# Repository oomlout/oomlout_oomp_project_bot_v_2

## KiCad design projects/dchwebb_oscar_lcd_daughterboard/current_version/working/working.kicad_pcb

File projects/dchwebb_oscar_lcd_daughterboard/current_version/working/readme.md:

# oscar
 
## summary 
* id: dchwebb_oscar_lcd_daughterboard
* user: dchwebb
* name: oscar
* board: lcd_daughterboard
* repo: https://github.com/dchwebb/Oscar
* src_file_repo_kicad_pcb: Hardware/lcd_Daughterboard.kicad_pcb
* src_file_repo_kicad_pcb_link: https://github.com/dchwebb/Oscar/tree/master/Hardware/lcd_Daughterboard.kicad_pcb
* src_file_repo_kicad_sch: Hardware/oscar.kicad_sch
* src_file_repo_kicad_sch_link: https://github.com/dchwebb/Oscar/tree/master/Hardware/oscar.kicad_sch

* src_file_repo_sch: Hardware/lcd_Daughterboard.sch
* src_file_repo_sch_link: https://github.com/dchwebb/Oscar/tree/master/Hardware/lcd_Daughterboard.sch
* full details link: https://github.com/oomlout/oomlout_oomp_project_bot_v_2/tree/main/projects/dchwebb_oscar_lcd_daughterboard/current_version/working

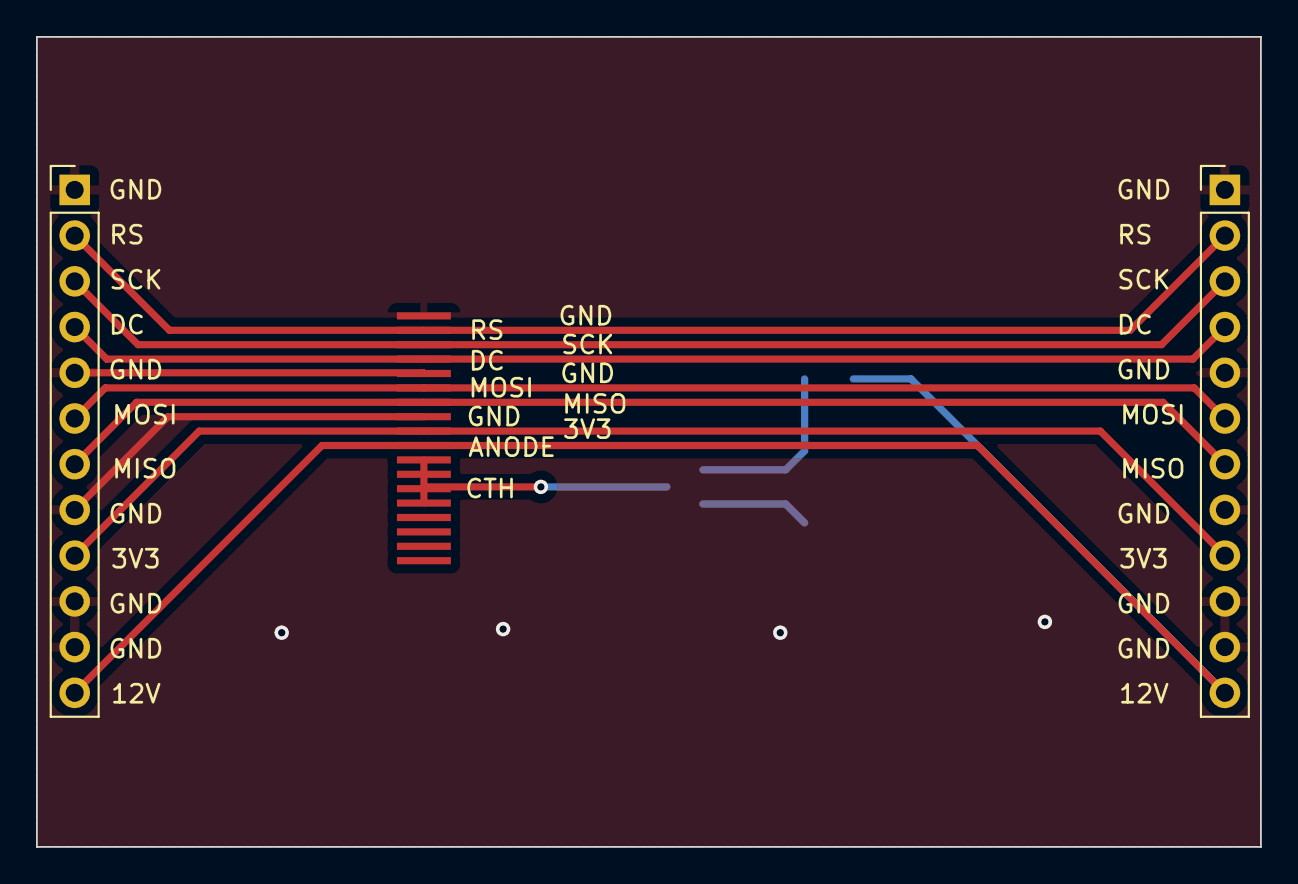
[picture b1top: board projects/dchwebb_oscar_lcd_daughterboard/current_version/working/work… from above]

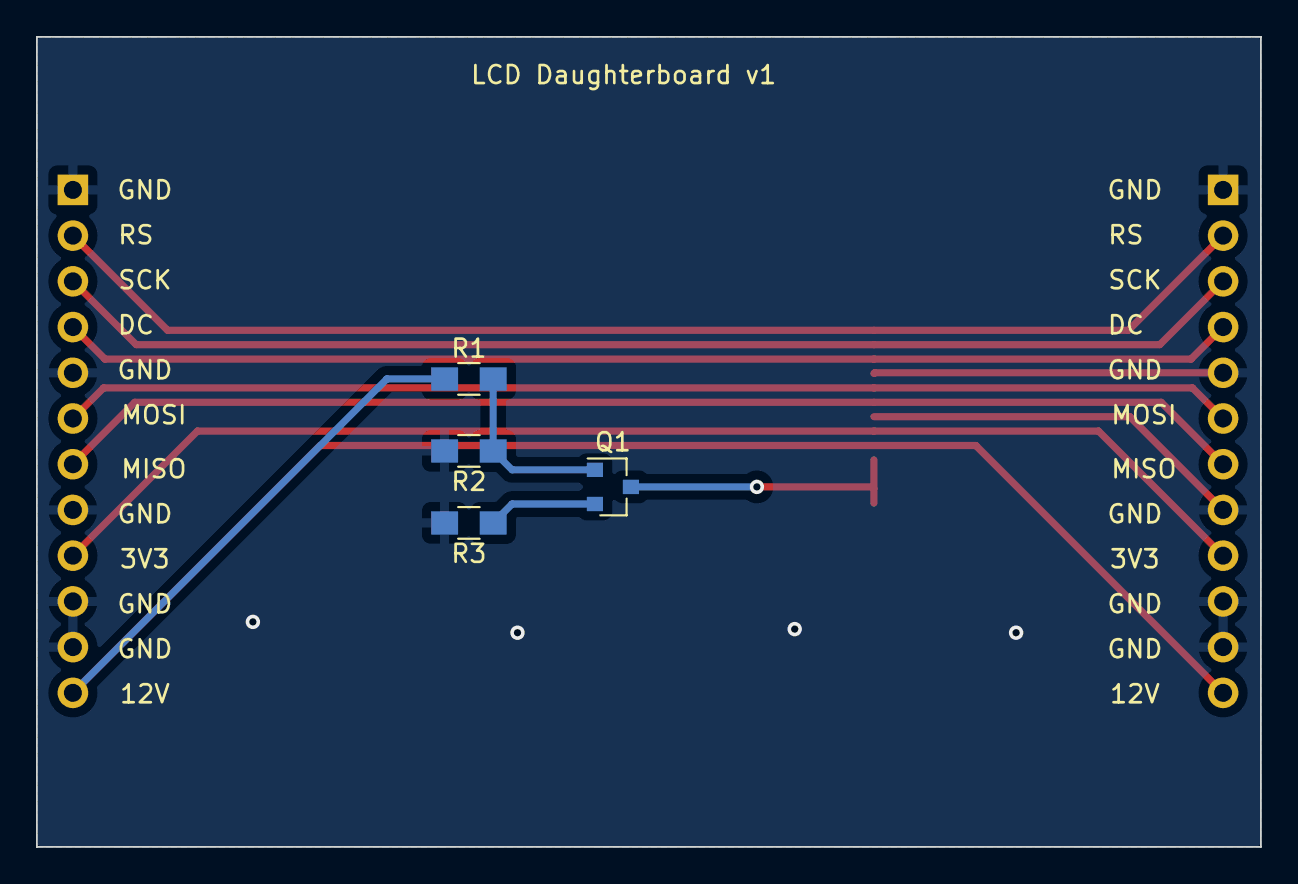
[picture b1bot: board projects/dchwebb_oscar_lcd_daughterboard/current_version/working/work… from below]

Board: 2 copper layers, 68.0 x 45.0 mm, 7 parts (4 on the bottom side), 11 nets.

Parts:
J1, J2: Conn_01x12; Pin_Header_Straight_1x12_Pitch2.54mm
Q1: MMBT3904; SOT-23
R1: 220; R_0805_HandSoldering
R2: 1k; R_0805_HandSoldering
R3: 100; R_0805_HandSoldering
U1: ILI9341_SPI_Bare; 18x0.8mmLCDConnector

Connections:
+3V3: J1.9, J2.9, U1.9
GND: J1.1, J1.5, J1.8, J1.10, J1.11, J2.1, J2.5, J2.8, J2.10, J2.11, R2.2, R3.2, U1.1, U1.5, U1.8
LCD_CATHODE: Q1.3, U1.11, U1.12, U1.13, U1.14
LCD_DC: J1.4, J2.4, U1.4
LCD_MISO: J1.7, J2.7, U1.7
LCD_MOSI: J1.6, J2.6, U1.6
LCD_RESET: J1.2, J2.2, U1.2
LCD_SCK: J1.3, J2.3, U1.3
unnamed: Q1.1, R1.2, R2.1
unnamed: Q1.2, R3.1
VCC: J1.12, J2.12, R1.1, U1.10

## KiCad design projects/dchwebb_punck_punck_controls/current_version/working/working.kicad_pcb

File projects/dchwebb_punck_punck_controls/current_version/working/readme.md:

# punck
 
## summary 
* id: dchwebb_punck_punck_controls
* user: dchwebb
* name: punck
* board: punck_controls
* repo: https://github.com/dchwebb/Punck
* src_file_repo_kicad_pcb: Hardware_v1_1/Punck_Components.kicad_pcb
* src_file_repo_kicad_pcb_link: https://github.com/dchwebb/Punck/tree/main/Hardware_v1_1/Punck_Components.kicad_pcb
* src_file_repo_kicad_sch: Hardware_v1_1/Punck_Components.kicad_sch
* src_file_repo_kicad_sch_link: https://github.com/dchwebb/Punck/tree/main/Hardware_v1_1/Punck_Components.kicad_sch

* src_file_repo_sch: 
* src_file_repo_sch_link: https://github.com/dchwebb/Punck/tree/main/
* full details link: https://github.com/oomlout/oomlout_oomp_project_bot_v_2/tree/main/projects/dchwebb_punck_punck_controls/current_version/working

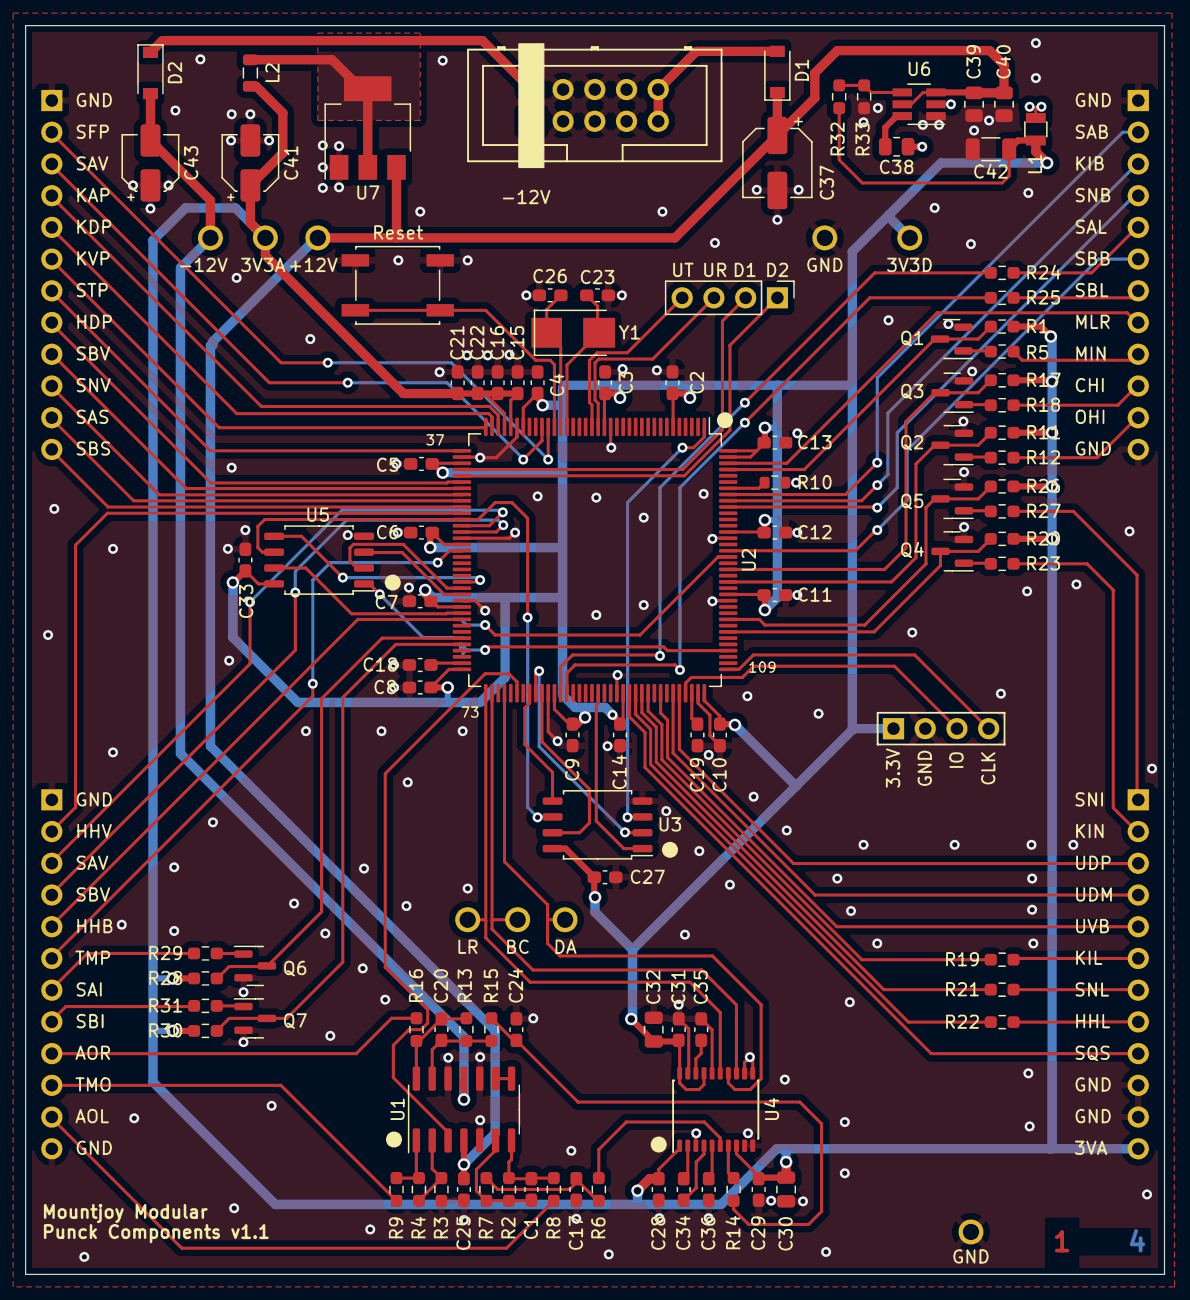
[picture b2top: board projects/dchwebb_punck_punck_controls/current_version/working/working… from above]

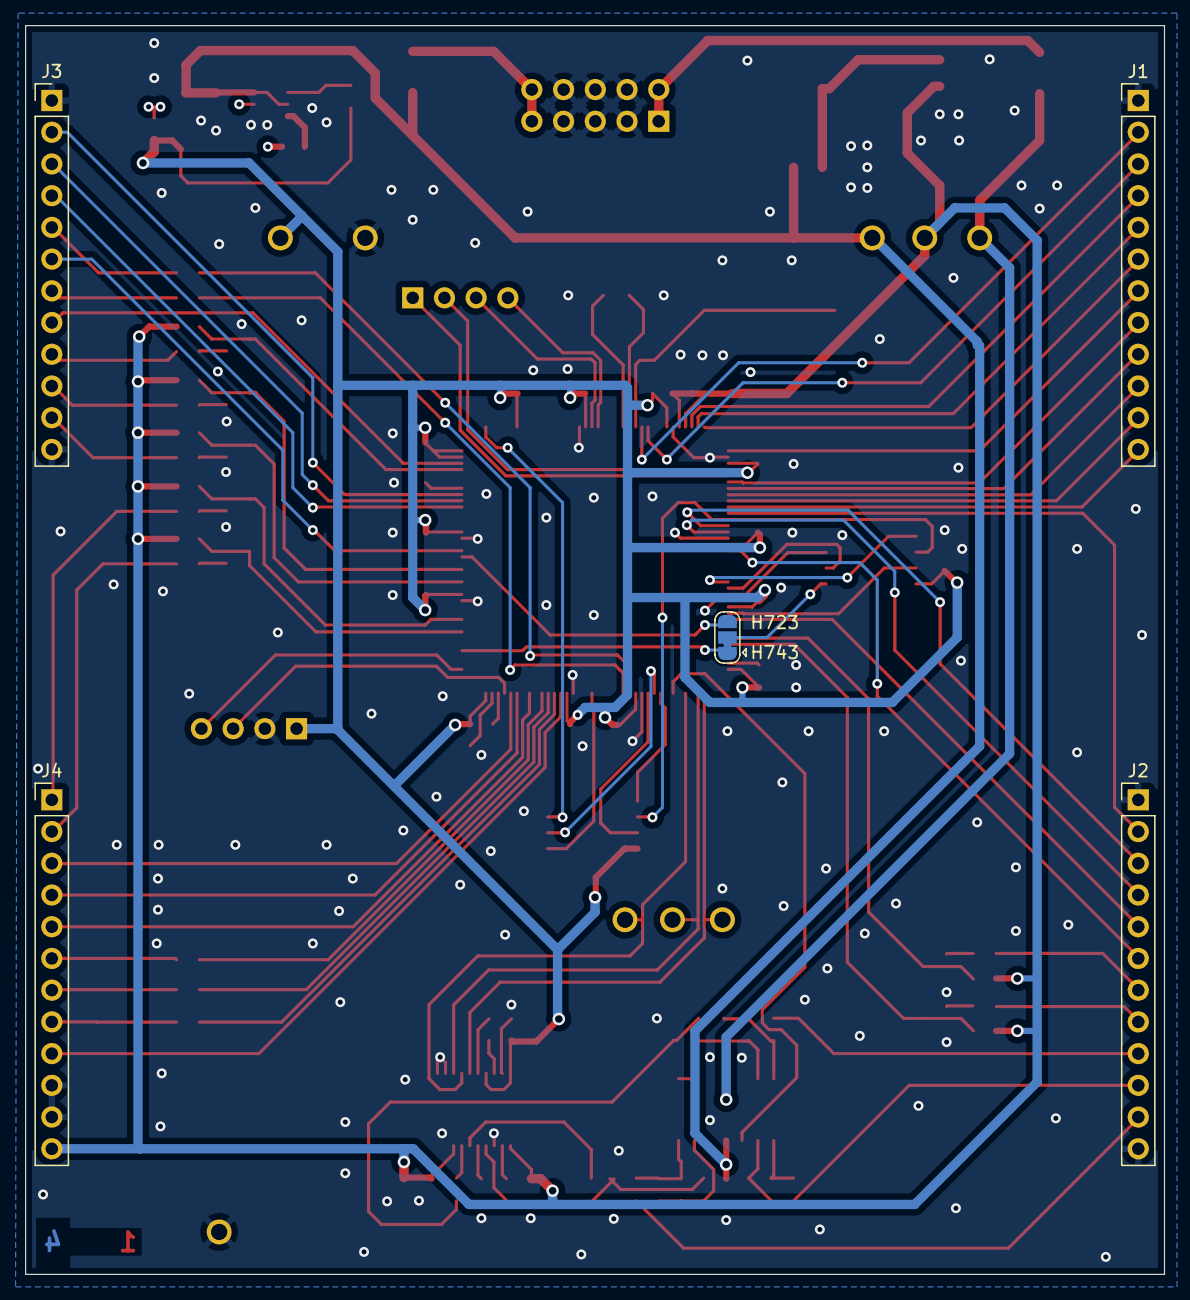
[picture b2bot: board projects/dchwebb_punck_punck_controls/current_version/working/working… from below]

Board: 4 copper layers, 91.2 x 100.0 mm, 114 parts (5 on the bottom side), 114 nets.

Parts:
C1, C20: 100pF; C_0603_1608Metric_Pad1.08x0.95mm_HandSolder
C2: 4.7uF; C_0603_1608Metric_Pad1.08x0.95mm_HandSolder
C3, C4, C5, C6, C7, C8, C9, C10, C11, C12, C13, C14, C15, C22, C27, C28, C29, C31, C33, C35: 100nF; C_0603_1608Metric_Pad1.08x0.95mm_HandSolder
C16, C21: 1uF; C_0603_1608Metric_Pad1.08x0.95mm_HandSolder
C17, C24: 2n2; C_0603_1608Metric_Pad1.08x0.95mm_HandSolder
C18, C19, C25, C34, C36: 2.2uF; C_0603_1608Metric_Pad1.08x0.95mm_HandSolder
C23, C26: 30pF; C_0603_1608Metric_Pad1.08x0.95mm_HandSolder
C30, C32: 10uF; C_0805_2012Metric
C37: 47uF; CP_Elec_5x5.8
C38: 100nF; R_0805_2012Metric
C39, C40: 10uF; R_0805_2012Metric
C41, C43: 22uF; CP_Elec_4x5.8
C42: 47uF; R_1206_3216Metric
D1, D2: 1N5819; D_SOD-123
FID1: 4_Layer_Marker; 4_Layer_Markers
J1, J2, J3, J4: Conn_01x12_Female; PinHeader_1x12_P2.54mm_Vertical
J5: Debug_Header; PinHeader_1x04_P2.54mm_Vertical
J6: SWD_Header; SWD_header
J7: Eurorack_10_pin_power; Eurorack_10_pin_header
JP1: QSPI2_NCS_Select; SolderJumper-3_P1.3mm_Bridged12_RoundedPad1.0x1.5mm
L1: 3.3uH; L_0806
L2: L; L_0805_2012Metric
Q1, Q2, Q3, Q4, Q5, Q6, Q7: MMBT3904; SOT-23
R1, R5, R11, R12, R17, R18, R20, R23, R26, R27, R28, R29, R30, R31: 4k7; R_0603_1608Metric_Pad0.98x0.95mm_HandSolder
R2, R13: 47k; R_0603_1608Metric_Pad0.98x0.95mm_HandSolder
R3, R7, R15: 15k; R_0603_1608Metric_Pad0.98x0.95mm_HandSolder
R4, R33: 10k; R_0603_1608Metric_Pad0.98x0.95mm_HandSolder
R6, R8, R9, R14, R16: 1k; R_0603_1608Metric_Pad0.98x0.95mm_HandSolder
R10: 100k; R_0603_1608Metric
R19, R21, R22, R24, R25: 560; R_0603_1608Metric_Pad0.98x0.95mm_HandSolder
R32: 33k; R_0603_1608Metric_Pad0.98x0.95mm_HandSolder
RESET1: SW_Push; SW_SPST_EVQQ2
TP1, TP2, TP3, TP4, TP5, TP6, TP7, TP8, TP9: TestPoint; 1.3mm_Test_Point
U1: TL074; SOIC-14_3.9x8.7mm_P1.27mm
U2: STM32H743ZITx; LQFP-144_20x20mm_P0.5mm
U3, U5: W25Q128JVS; SOIC-8_5.23x5.23mm_P1.27mm
U4: PCM5100APW; SSOP-20_4.4x6.5mm_Pitch0.65mm_Round_Pads
U6: TPS561201; SOT-23-6_Handsoldering
U7: LD1117-3.3-4Tab; SOT-223-3_TabPin2
Y1: 8MHz 20pF; Crystal_SMD_5032-2Pin_5.0x3.2mm

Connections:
+3.3VA: C15.2, C16.2, C21.2, C22.2, C28.1, C29.1, C30.1, C41.1, J4.12, L2.1, R1.2, R11.2, R17.2, R20.2, R26.2, R28.2, R30.2, TP6.1, U2.32 (VREF+), U2.33 (VDDA), U4.1 (CPVDD), U4.8 (AVDD)
+3V3: C2.2, C3.2, C4.2, C5.2, C6.2, C7.2, C8.2, C9.2, C10.2, C11.2, C12.2, C13.2, C14.2, C27.1, C31.1, C32.1, C33.1, C42.1, J6.1, L1.2, R32.1, TP5.1, U2.6 (VBAT), U2.17 (VDD), U2.30 (VDD), U2.39 (VDD), U2.52 (VDD), U2.62 (VDD), U2.72 (VDD), U2.84 (VDD), U2.95 (VDD33_USB), U2.108 (VDD), U2.121 (VDD), U2.131 (VDD), U2.143 (PDR_ON), U2.144 (VDD), U3.8 (VCC), U4.17 (XSMT), U4.20 (DVDD), U5.8 (VCC)
+12V: D1.2 (A), J7.9, J7.10
-12V: D2.1 (K), J7.1, J7.2
/AUDIO_OUT_L: J2.11, R8.2
/AUDIO_OUT_R: J2.9, R16.2
/CB: C38.2, U6.6 (VBST)
/CH_CLAMP: Q3.3 (C), R17.1, U2.125 (PG10)
/CH_IN: J3.10, R18.1
/DAC1: J5.2, U2.40 (PA4)
/DAC2: J5.1, U2.41 (PA5)
/DAC_BCLK: TP3.1, U2.74 (PB13), U4.13 (BCK)
/DAC_DATA: TP2.1, U2.76 (PB15), U4.14 (DIN)
/DAC_LRCLK: TP1.1, U2.73 (PB12), U4.15 (LRCK)
/DAC_OUT_L: R6.2, U4.6 (OUTL)
/DAC_OUT_R: R14.2, U4.7 (OUTR)
/FB: R32.2, R33.1, U6.4 (VFB)
/HH_BTN: J2.5, U2.64 (PE11)
/HH_LED: J4.8, R22.1
/HH_LED_OUT: R22.2, U2.97 (PC7)
/HIHAT_DECAY_POT: J1.8, U2.42 (PA6)
/HIHAT_VOL_POT: J2.2, U2.47 (PB1)
/KICK_ATTACK_POT: J1.4, U2.34 (PA0)
/KICK_CLAMP: Q4.3 (C), R20.1, U2.115 (PD1)
/KICK_DECAY_POT: J1.5, U2.35 (PA1)
/KICK_IN: J4.2, R23.1
/KICK_VOL_POT: J1.6, U2.36 (PA2)
/KI_BTN: J3.3, U2.136 (PB6)
/KI_LED: J4.6, R19.1
/KI_LED_OUT: R19.2, U2.99 (PC9)
/MIDI_IN: J3.9, R5.1
/MIDI_LEARN: J3.8, U2.142 (PE1)
/MIDI_UART: Q1.3 (C), R1.1, U2.141 (PE0)
/OCTOSPIM_P2_NCS: JP1.3 (B), U2.127 (PG12)
/OH_CLAMP: Q2.3 (C), R11.1, U2.123 (PD7)
/OH_IN: J3.11, R12.1
/QSPI_BK1_IO0: U2.80 (PD11), U3.5 (DI(IO0))
/QSPI_BK1_IO1: U2.81 (PD12), U3.2 (DO(IO1))
/QSPI_BK1_IO2: U2.1 (PE2), U3.3 (IO2)
/QSPI_BK1_IO3: U2.82 (PD13), U3.7 (IO3)
/QSPI_BK1_NCS: U2.91 (PG6), U3.1 (~CS)
/QSPI_BK2_IO0: U2.58 (PE7), U5.5 (DI(IO0))
/QSPI_BK2_IO1: U2.59 (PE8), U5.2 (DO(IO1))
/QSPI_BK2_IO2: U2.60 (PE9), U5.3 (IO2)
/QSPI_BK2_IO3: U2.63 (PE10), U5.7 (IO3)
/QSPI_BK2_NCS: JP1.1 (A), U2.112 (PC11)
/QSPI_CLK: U2.48 (PB2), U3.6 (CLK), U5.6 (CLK)
/SAMPLER_A_CLAMP: Q6.3 (C), R28.1, U2.67 (PE14)
/SAMPLER_A_IN: J2.7, R29.1
/SAMPLER_A_SPEED_POT: J1.11, U2.45 (PC5)
/SAMPLER_A_VOICE_POT: J1.3, U2.27 (PC1)
/SAMPLER_A_VOL_POT: J2.3, U2.49 (PF11)
/SAMPLER_B_CLAMP: Q7.3 (C), R30.1, U2.68 (PE15)
/SAMPLER_B_IN: J2.8, R31.1
/SAMPLER_B_SPEED_POT: J1.12, U2.46 (PB0)
/SAMPLER_B_VOICE_POT: J1.9, U2.43 (PA7)
/SAMPLER_B_VOL_POT: J2.4, U2.50 (PF12)
/SA_BTN: J3.2, U2.137 (PB7)
/SA_LED: J3.5, R24.1
/SA_LED_OUT: R24.2, U2.85 (PD14)
/SB_BTN: J3.6, U2.128 (PG13)
/SB_LED: J3.7, R25.1
/SB_LED_OUT: R25.2, U2.86 (PD15)
/SEQ_SELECT: J4.9, U2.96 (PC6)
/SNARE_CLAMP: Q5.3 (C), R26.1, U2.117 (PD3)
/SNARE_FILTER_POT: J1.2, U2.26 (PC0)
/SNARE_IN: J4.1, R27.1
/SNARE_TUNING_POT: J1.7, U2.37 (PA3)
/SNARE_VOL_POT: J1.10, U2.44 (PC4)
/SN_BTN: J3.4, U2.135 (PB5)
/SN_LED: J4.7, R21.1
/SN_LED_OUT: R21.2, U2.98 (PC8)
/SWCLK: J6.4, U2.109 (PA14)
/SWIO: J6.3, U2.105 (PA13)
/TEMPO_CLOCK: U1.3 (+), U2.78 (PD9)
/TEMPO_OUT: J2.10, R9.2
/TEMPO_POT: J2.6, U2.53 (PF13)
/UART_RX: J5.3, U2.18 (PF6)
/UART_TX: J5.4, U2.19 (PF7)
/USB_DM: J4.4, U2.103 (PA11)
/USB_DP: J4.3, U2.104 (PA12)
/USB_VBUS: J4.5, U2.101 (PA9)
/VO: L2.2, U7.2 (VO)
/VSW: C38.1, L1.1, U6.2 (SW)
GND: C2.1, C3.1, C4.1, C5.1, C6.1, C7.1, C8.1, C9.1, C10.1, C11.1, C12.1, C13.1, C14.1, C15.1, C16.1, C17.2, C18.2, C19.2, C21.1, C22.1, C23.2, C24.2, C25.2, C26.2, C27.2, C28.2, C29.2, C30.2, C31.2, C32.2, C33.2, C35.1, C36.2, C37.2, C39.2, C40.2, C41.2, C42.2, C43.1, J1.1, J2.1, J2.12, J3.1, J3.12, J4.10, J4.11, J6.2, J7.3, J7.4, J7.5, J7.6, J7.7, J7.8, Q1.2 (E), Q2.2 (E), Q3.2 (E), Q4.2 (E), Q5.2 (E), Q6.2 (E), Q7.2 (E), R3.2, R10.1, R33.2, RESET1.2, TP4.1, TP9.1, U1.5 (+), U1.10 (+), U1.12 (+), U2.16 (VSS), U2.31 (VSSA), U2.38 (VSS), U2.51 (VSS), U2.61 (VSS), U2.83 (VSS), U2.94 (VSS), U2.107 (VSS), U2.120 (VSS), U2.130 (VSS), U3.4 (GND), U4.3 (CPGND), U4.9 (AGND), U4.10 (DEMP), U4.11 (FLT), U4.12 (SCK), U4.16 (FMT), U4.19 (DGND), U5.4 (GND), U6.1 (GND), U7.1 (GND)
unnamed: C1.1, R2.1, R8.1, U1.7
unnamed: C1.2, R2.2, R7.1, U1.6 (-)
unnamed: C17.1, R6.1, R7.2
unnamed: C18.1, U2.71 (VCAP1)
unnamed: C19.1, U2.106 (VCAP2)
unnamed: C20.1, R13.1, R16.1, U1.14
unnamed: C20.2, R13.2, R15.1, U1.13 (-)
unnamed: C23.1, U2.23 (PH0), Y1.2
unnamed: C24.1, R14.1, R15.2
unnamed: C26.1, U2.24 (PH1), Y1.1
unnamed: C34.1, U4.2 (CAPP)
unnamed: C34.2, U4.4 (CAPM)
unnamed: C35.2, U4.18 (LDOO)
unnamed: C36.1, U4.5 (VNEG)
unnamed: JP1.2 (C), U5.1 (~CS)
unnamed: Q1.1 (B), R5.2
unnamed: Q2.1 (B), R12.2
unnamed: Q3.1 (B), R18.2
unnamed: Q4.1 (B), R23.2
unnamed: Q5.1 (B), R27.2
unnamed: Q6.1 (B), R29.2
unnamed: Q7.1 (B), R31.2
unnamed: R3.1, R4.2, U1.2 (-)
unnamed: R4.1, R9.1, U1.1
unnamed: R10.2, U2.138 (BOOT0)
unnamed: RESET1.1, U2.25 (NRST)
unnamed: U1.8, U1.9 (-)
VCC: C25.1, C37.1, C39.1, C40.1, D1.1 (K), TP7.1, U1.4 (V+), U6.3 (VIN), U6.5 (EN), U7.3 (VI)
VEE: C43.2, D2.2 (A), TP8.1, U1.11 (V-)

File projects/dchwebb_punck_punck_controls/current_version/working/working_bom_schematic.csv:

"Source:","C:\gh\oomlout_oomp_project_bot_v_2\projects\dchwebb_punck_punck_controls\current_version\working\working.kicad_sch"
"Date:","01/10/2023 02:41:31"
"Tool:","Eeschema 7.0.6"
"Generator:","C:/Program Files/KiCad/7.0/bin/scripting/plugins/bom_csv_grouped_by_value_with_fp.py"
"Component Count:","114"
"Ref","Qnty","Value","Cmp name","Footprint","Description","Vendor","DNP"
"C1, C20","2","100pF","C_Small","Capacitor_SMD:C_0603_1608Metric_Pad1.08x0.95mm_HandSolder","Unpolarized capacitor, small symbol","",""
"C2","1","4.7uF","C_Small","Capacitor_SMD:C_0603_1608Metric_Pad1.08x0.95mm_HandSolder","Unpolarized capacitor, small symbol","",""
"C3, C4, C5, C6, C7, C8, C9, C10, C11, C12, C13, C14, C15, C22, C27, C28, C29, C31, C33, C35","20","100nF","C_Small","Capacitor_SMD:C_0603_1608Metric_Pad1.08x0.95mm_HandSolder","Unpolarized capacitor, small symbol","",""
"C16, C21","2","1uF","C_Small","Capacitor_SMD:C_0603_1608Metric_Pad1.08x0.95mm_HandSolder","Unpolarized capacitor, small symbol","",""
"C17, C24","2","2n2","C_Small","Capacitor_SMD:C_0603_1608Metric_Pad1.08x0.95mm_HandSolder","Unpolarized capacitor, small symbol","",""
"C18, C19, C25, C34, C36","5","2.2uF","C_Small","Capacitor_SMD:C_0603_1608Metric_Pad1.08x0.95mm_HandSolder","Unpolarized capacitor, small symbol","",""
"C23, C26","2","30pF","C_Small","Capacitor_SMD:C_0603_1608Metric_Pad1.08x0.95mm_HandSolder","Unpolarized capacitor, small symbol","",""
"C30, C32, C39, C40","4","10uF","C_Small","Capacitor_SMD:C_0805_2012Metric","Unpolarized capacitor, small symbol","",""
"C37","1","47uF","C_Polarized_Small","Capacitor_SMD:CP_Elec_5x5.8","Polarized capacitor, small symbol","",""
"C38","1","100nF","C_Small","Capacitor_SMD:C_0805_2012Metric","Unpolarized capacitor, small symbol","",""
"C41, C43","2","22uF","C_Polarized_Small","Capacitor_SMD:CP_Elec_4x5.8","Polarized capacitor, small symbol","",""
"C42","1","47uF","C_Small","Resistor_SMD:R_1206_3216Metric","Unpolarized capacitor, small symbol","",""
"D1, D2","2","1N5819","1N5819","Diode_SMD:D_SOD-123","40V 1A Schottky Barrier Rectifier Diode, DO-41","",""
"FID1","1","4_Layer_Marker","Fiducial","Custom_Footprints:4_Layer_Markers","Fiducial Marker","",""
"J1, J2, J3, J4","4","Conn_01x12_Female","Conn_01x12_Female","Connector_PinHeader_2.54mm:PinHeader_1x12_P2.54mm_Vertical","Generic connector, single row, 01x12, script generated (kicad-library-utils/schlib/autogen/connector/)","",""
"J5","1","Debug_Header","Conn_01x04_Female","Connector_PinHeader_2.54mm:PinHeader_1x04_P2.54mm_Vertical","Generic connector, single row, 01x04, script generated (kicad-library-utils/schlib/autogen/connector/)","",""
"J6","1","SWD_Header","Conn_01x04_Male","Custom_Footprints:SWD_header","Generic connector, single row, 01x04, script generated (kicad-library-utils/schlib/autogen/connector/)","",""
"J7","1","Eurorack_10_pin_power","Eurorack_10_pin_power","Custom_Footprints:Eurorack_10_pin_header","","",""
"JP1","1","QSPI2_NCS_Select","SolderJumper_3_Bridged12","Jumper:SolderJumper-3_P1.3mm_Bridged12_RoundedPad1.0x1.5mm","3-pole Solder Jumper, pins 1+2 closed/bridged","",""
"L1","1","3.3uH","L_Small","Custom_Footprints:L_0806","Inductor, small symbol","",""
"L2","1","L","L","Inductor_SMD:L_0805_2012Metric","Inductor","",""
"Q1, Q2, Q3, Q4, Q5, Q6, Q7","7","MMBT3904","MMBT3904","Package_TO_SOT_SMD:SOT-23","0.2A Ic, 40V Vce, Small Signal NPN Transistor, SOT-23","",""
"R1, R5, R11, R12, R17, R18, R20, R23, R26, R27, R28, R29, R30, R31","14","4k7","R_Small","Resistor_SMD:R_0603_1608Metric_Pad0.98x0.95mm_HandSolder","Resistor, small symbol","",""
"R2, R13","2","47k","R","Resistor_SMD:R_0603_1608Metric_Pad0.98x0.95mm_HandSolder","Resistor","",""
"R3, R7, R15","3","15k","R","Resistor_SMD:R_0603_1608Metric_Pad0.98x0.95mm_HandSolder","Resistor","",""
"R4, R33","2","10k","R_Small","Resistor_SMD:R_0603_1608Metric_Pad0.98x0.95mm_HandSolder","Resistor, small symbol","",""
"R6, R8, R9, R14, R16","5","1k","R_Small","Resistor_SMD:R_0603_1608Metric_Pad0.98x0.95mm_HandSolder","Resistor, small symbol","",""
"R10","1","100k","R_Small","Resistor_SMD:R_0603_1608Metric","Resistor, small symbol","",""
"R19, R21, R22, R24, R25","5","560","R_Small","Resistor_SMD:R_0603_1608Metric_Pad0.98x0.95mm_HandSolder","Resistor, small symbol","",""
"R32","1","33k","R_Small","Resistor_SMD:R_0603_1608Metric_Pad0.98x0.95mm_HandSolder","Resistor, small symbol","",""
"RESET1","1","SW_Push","SW_Push","Custom_Footprints:SW_SPST_EVQQ2","Push button switch, generic, two pins","",""
"TP1, TP2, TP3, TP4, TP5, TP6, TP7, TP8, TP9","9","TestPoint","TestPoint","Custom_Footprints:1.3mm_Test_Point","test point","",""
"U1","1","TL074","TL074","Package_SO:SOIC-14_3.9x8.7mm_P1.27mm","Quad Low-Noise JFET-Input Operational Amplifiers, DIP-14/SOIC-14","",""
"U2","1","STM32H743ZITx","STM32H743ZITx","Package_QFP:LQFP-144_20x20mm_P0.5mm","ARM Cortex-M7 MCU, 2048KB flash, 864KB RAM, 400MHz, 1.7-3.6V, 114 GPIO, LQFP-144","",""
"U3, U5","2","W25Q128JVS","W25Q128JVS","Package_SO:SOIC-8_5.23x5.23mm_P1.27mm","128Mb Serial Flash Memory, Standard/Dual/Quad SPI, SOIC-8","",""
"U4","1","PCM5100APW","PCM5100APW","Custom_Footprints:SSOP-20_4.4x6.5mm_Pitch0.65mm_Round_Pads","2VRMS DirectPath, 100dB Audio Stereo DAC with 32-bit, 384kHz PCM Interface, TSSOP-20","",""
"U6","1","TPS561201","TPS561201","Package_TO_SOT_SMD:SOT-23-6_Handsoldering","1A Synchronous Step-Down Voltage Regulator, Adjustable Output Voltage, 4.5-17V Input Voltage, SOT-23-6","",""
"U7","1","LD1117-3.3-4Tab","LD1117-3.3-4Tab","Package_TO_SOT_SMD:SOT-223-3_TabPin2","1A Low Dropout regulator, positive, 3.3V fixed output, SOT-223","",""
"Y1","1","8MHz 20pF","Crystal","Crystal:Crystal_SMD_5032-2Pin_5.0x3.2mm","Two pin crystal","",""

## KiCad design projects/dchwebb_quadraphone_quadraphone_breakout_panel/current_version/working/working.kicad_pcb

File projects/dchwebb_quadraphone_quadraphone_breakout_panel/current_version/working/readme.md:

# quadraphone
 
## summary 
* id: dchwebb_quadraphone_quadraphone_breakout_panel
* user: dchwebb
* name: quadraphone
* board: quadraphone_breakout_panel
* repo: https://github.com/dchwebb/Quadraphone
* src_file_repo_kicad_pcb: V1_Production/Quadraphone.kicad_pcb
* src_file_repo_kicad_pcb_link: https://github.com/dchwebb/Quadraphone/tree/main/V1_Production/Quadraphone.kicad_pcb
* src_file_repo_kicad_sch: V1_Production/OSCVoice.kicad_sch
* src_file_repo_kicad_sch_link: https://github.com/dchwebb/Quadraphone/tree/main/V1_Production/OSCVoice.kicad_sch

* src_file_repo_sch: 
* src_file_repo_sch_link: https://github.com/dchwebb/Quadraphone/tree/main/
* full details link: https://github.com/oomlout/oomlout_oomp_project_bot_v_2/tree/main/projects/dchwebb_quadraphone_quadraphone_breakout_panel/current_version/working

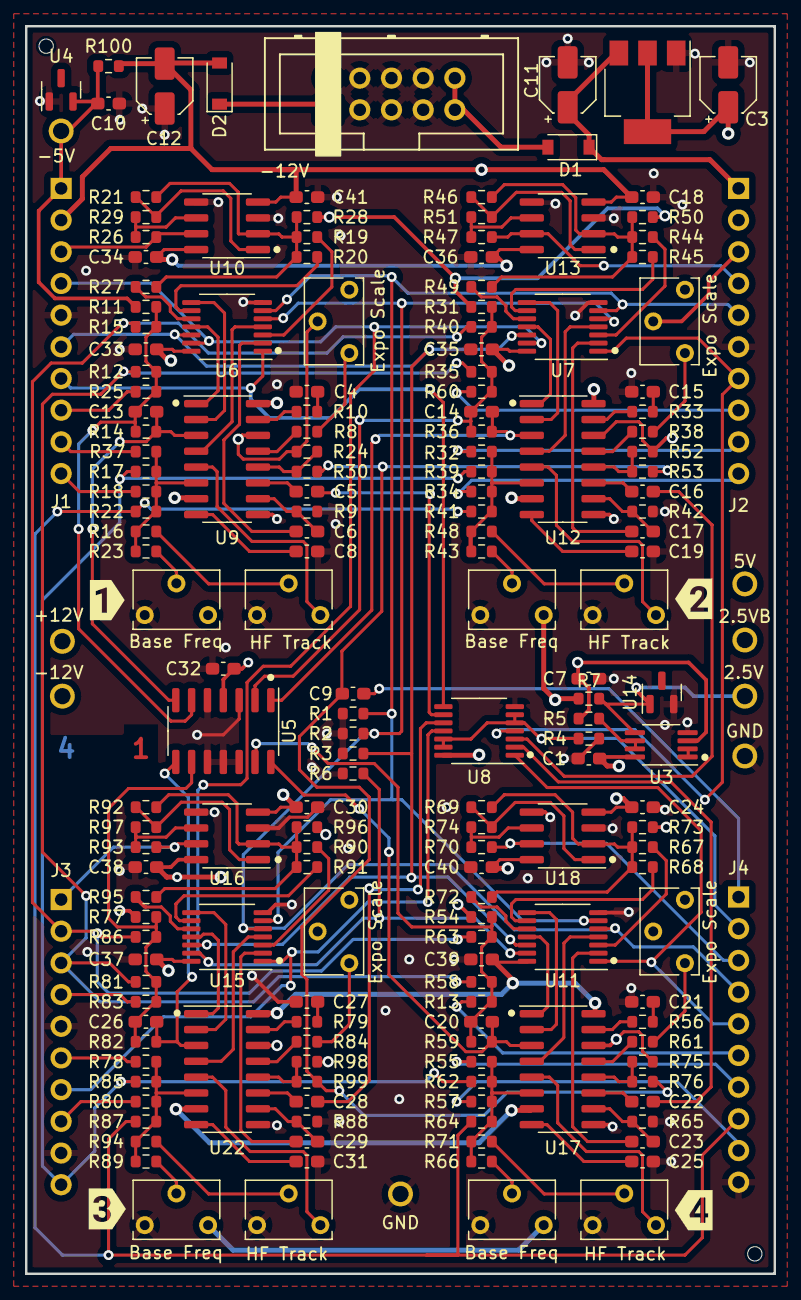
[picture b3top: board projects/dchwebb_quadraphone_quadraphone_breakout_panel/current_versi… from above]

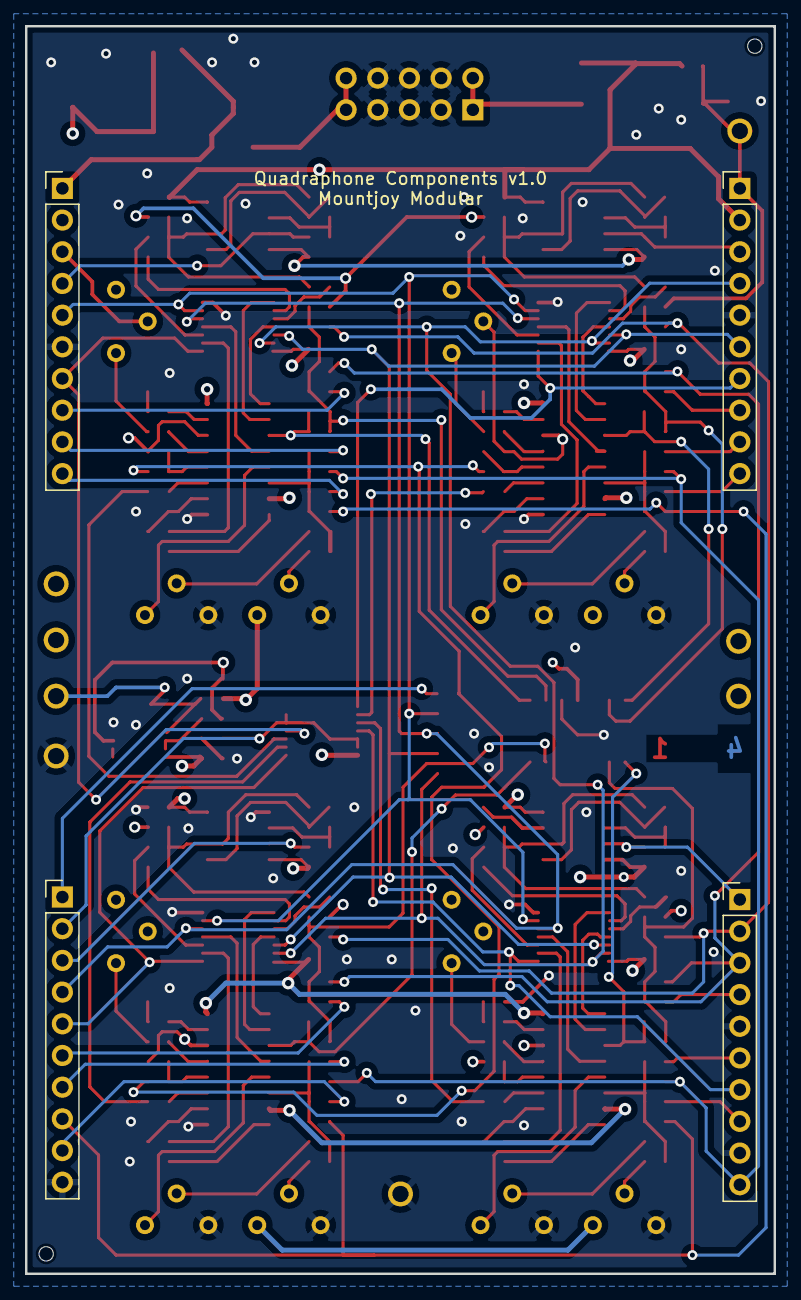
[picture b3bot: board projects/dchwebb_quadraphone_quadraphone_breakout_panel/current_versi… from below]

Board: 4 copper layers, 60.0 x 100.0 mm, 190 parts (4 on the bottom side), 142 nets.

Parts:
Base_Freq_Trim1, Base_Freq_Trim2, Base_Freq_Trim3, Base_Freq_Trim4: 5k; Potentiometer_Bourns_3266W_Vertical
C1, C7, C9: 1uF; C_0603_1608Metric_Pad1.08x0.95mm_HandSolder
C3: 10uF; CP_Elec_4x5.7
C4, C5, C6, C15, C16, C17, C21, C22, C23, C27, C28, C29: 10nF; C_0603_1608Metric_Pad1.08x0.95mm_HandSolder
C8, C19, C25, C31: 3.9nF; C_0603_1608Metric_Pad1.08x0.95mm_HandSolder
C10, C18, C24, C30, C32, C33, C34, C35, C36, C37, C38, C39, C40, C41: 100nF; C_0603_1608Metric_Pad1.08x0.95mm_HandSolder
C11, C12: 22uF; CP_Elec_4x5.8
C13, C14, C20, C26: 1nF; C_0603_1608Metric_Pad1.08x0.95mm_HandSolder
D1, D2: 1N5819; D_SOD-123
Expo_Trim1, Expo_Trim2, Expo_Trim3, Expo_Trim4: 5k; Potentiometer_Bourns_3266W_Vertical
FID1: 4_Layer_Marker; 4_Layer_Markers
HF_Track_Trim1, HF_Track_Trim2, HF_Track_Trim3, HF_Track_Trim4: 5k; Potentiometer_Bourns_3266W_Vertical
J1, J2, J3, J4: Conn_01x10_Male; PinHeader_1x10_P2.54mm_Vertical
J5: Eurorack_10_pin_power; Eurorack_10_pin_header
R1, R2, R3, R4, R6: 14k; R_0603_1608Metric
R5: 100; R_0603_1608Metric
R7: 2k7; R_0603_1608Metric
R8, R38, R61, R84: 22k; R_0603_1608Metric
R9, R42, R65, R88: 10k; R_0603_1608Metric
R10, R16, R33, R48, R56, R71, R79, R94: 267; R_0603_1608Metric
R11, R31, R54, R77: 47k; R_0603_1608Metric
R12, R21, R28, R35, R46, R50, R58, R69, R73, R81, R92, R96: 120k; R_0603_1608Metric
R13, R15, R17, R25, R39, R40, R60, R62, R63, R83, R85, R86: 100k; R_0603_1608Metric
R14, R36, R59, R82: 13k; R_0603_1608Metric
R18, R22, R23, R32, R34, R37, R41, R43, R55, R57, R64, R66, R78, R80, R87, R89: 49.9k; R_0603_1608Metric
R19, R20, R27, R44, R45, R49, R67, R68, R72, R90, R91, R95: 30k; R_0603_1608Metric
R24, R52, R75, R98: 499k; R_0603_1608Metric
R26, R47, R70, R93: 36k; R_0603_1608Metric
R29, R51, R74, R97: 18k; R_0603_1608Metric
R30, R53, R76, R99: 1M; R_0603_1608Metric
R100: 2.2k; R_0603_1608Metric
TP1, TP2, TP3, TP4, TP5, TP6, TP7, TP8: TestPoint; 1.3mm_Test_Point
U1: AMS1117-5.0; SOT-223-3_TabPin2
U3: MCP6002; MSOP-8_3x3mm_P0.65mm
U4: LM4040DBZ-5; SOT-23
U5: MCP6004; SOIC-14_3.9x8.7mm_P1.27mm
U6, U7, U8, U11, U15: 4066; TSSOP-14_4.4x5mm_P0.65mm
U9, U12, U17, U22: SSI2131; SOIC-16_3.9x9.9mm_P1.27mm
U10, U13, U16, U18: TL072; SOIC-8_3.9x4.9mm_P1.27mm
U14: LM4040DBZ-2.5; SOT-23
kibuzzard-63D3EB0F: G***; kibuzzard-63D3EB0F
kibuzzard-63D3EB2D: G***; kibuzzard-63D3EB2D
kibuzzard-63D3EB3D: G***; kibuzzard-63D3EB3D
kibuzzard-63D3EB53: G***; kibuzzard-63D3EB53

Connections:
+2V5: C7.2, C32.1, Expo_Trim1.2, Expo_Trim2.2, Expo_Trim3.2, Expo_Trim4.2, J2.3, R5.2, R24.2, R52.2, R75.2, R98.2, TP3.1, U3.3 (+), U5.4 (V+), U9.14 (VREF), U12.14 (VREF), U17.14 (VREF), U22.14 (VREF)
+5V: Base_Freq_Trim1.3, Base_Freq_Trim2.3, Base_Freq_Trim3.3, Base_Freq_Trim4.3, C1.1, C3.1, C33.1, C35.1, C37.1, C39.1, J2.2, R7.1, TP2.1, U1.2 (VO), U3.8 (V+), U6.14 (VDD), U7.14 (VDD), U8.14 (VDD), U9.16 (VDD), U11.14 (VDD), U12.16 (VDD), U15.14 (VDD), U17.16 (VDD), U22.16 (VDD)
+12V: C11.1, C34.1, C36.1, C38.1, C40.1, D1.1 (K), J2.1, TP1.1, U1.3 (VI), U10.8 (V+), U13.8 (V+), U16.8 (V+), U18.8 (V+)
-5V: C10.1, J1.1, R11.2, R28.2, R31.2, R50.2, R54.2, R73.2, R77.2, R96.2, R100.2, TP6.1, U4.2 (A)
-12V: C12.2, C18.1, C24.1, C30.1, C41.1, D2.2 (A), J1.2, R100.1, TP7.1, U9.7 (VSS), U10.4 (V-), U12.7 (VSS), U13.4 (V-), U16.4 (V-), U17.7 (VSS), U18.4 (V-), U22.7 (VSS)
/2.5V_Test: R7.2, TP8.1, U3.5 (+), U14.1 (K)
/+12V_IN: D1.2 (A), J5.9, J5.10
/-12V_IN: D2.1 (K), J5.1, J5.2
/FINE_TUNE: J3.10, R17.1, R39.1, R62.1, R85.1
/FREQ_MOD1: J1.10, R18.1
/FREQ_MOD2: J2.10, R34.1
/FREQ_MOD3: J3.8, R80.1
/FREQ_MOD4: J4.9, R57.1
/HARD_SYNCH_SW: J1.4, R6.2, U6.13, U7.13, U11.13, U15.13
/LIN_FREQ_IN: C9.1, J4.1
/Linear_Frequency: C9.2, R30.1, R53.1, R76.1, R99.1
/MIX_OUT1: J1.3, R26.1, U10.7
/MIX_OUT2: J2.4, R47.1, U13.7
/MIX_OUT3: J3.1, R93.1, U16.7
/MIX_OUT4: J4.3, R70.1, U18.7
/OCT_TUNE: J4.8, R22.1, R41.1, R64.1, R87.1
/OSCVoice1/BW_Comp: R10.1, U9.15 (BW_COMP)
/OSCVoice1/Expo_Freq: R16.2, R17.2, R18.2, R22.2, R23.2, R37.2, U9.6 (EXPO_FREQ)
/OSCVoice1/HF_Track: HF_Track_Trim1.3, U9.5 (HF_TRACK)
/OSCVoice1/Hard_Synch: C6.2, U6.2
/OSCVoice1/Linear_Frequency: R24.1, R30.2, U9.12 (LIN_FREQ)
/OSCVoice1/MIX_1: R21.1, R29.2, U10.1
/OSCVoice1/Op_Amp_Mix: R19.1, R20.1, R21.2, R27.1, R28.1, U10.2 (-)
/OSCVoice1/PWM_Control: C13.2, R14.1, U5.7, U9.3 (PWM_CTRL)
/OSCVoice1/PWM_Opamp_Mix: C13.1, R11.1, R12.1, R14.2, R15.1, R25.1, U5.6 (-)
/OSCVoice1/Pulse_Mix: R20.2, U6.9
/OSCVoice1/Pulse_Out: U6.8, U9.2 (PULSE_OUT)
/OSCVoice1/Saw_Mix: R27.2, U6.10
/OSCVoice1/Saw_Out: U6.11, U9.1 (SAW_OUT)
/OSCVoice1/Soft_Synch: C5.2, U8.9
/OSCVoice1/Triangle_Mix: R19.2, U6.3
/OSCVoice1/Triangle_Out: U6.4, U9.4 (TRI_OUT)
/OSCVoice2/BW_Comp: R33.1, U12.15 (BW_COMP)
/OSCVoice2/Expo_Freq: R32.2, R34.2, R39.2, R41.2, R43.2, R48.2, U12.6 (EXPO_FREQ)
/OSCVoice2/HF_Track: HF_Track_Trim2.3, U12.5 (HF_TRACK)
/OSCVoice2/Hard_Synch: C17.2, U7.2
/OSCVoice2/Linear_Frequency: R52.1, R53.2, U12.12 (LIN_FREQ)
/OSCVoice2/MIX_1: R46.1, R51.2, U13.1
/OSCVoice2/Op_Amp_Mix: R44.1, R45.1, R46.2, R49.1, R50.1, U13.2 (-)
/OSCVoice2/PWM_Control: C14.2, R36.1, U5.1, U12.3 (PWM_CTRL)
/OSCVoice2/PWM_Opamp_Mix: C14.1, R31.1, R35.1, R36.2, R40.1, R60.1, U5.2 (-)
/OSCVoice2/Pulse_Mix: R45.2, U7.9
/OSCVoice2/Pulse_Out: U7.8, U12.2 (PULSE_OUT)
/OSCVoice2/Saw_Mix: R49.2, U7.10
/OSCVoice2/Saw_Out: U7.11, U12.1 (SAW_OUT)
/OSCVoice2/Soft_Synch: C16.2, U8.3
/OSCVoice2/Triangle_Mix: R44.2, U7.3
/OSCVoice2/Triangle_Out: U7.4, U12.4 (TRI_OUT)
/OSCVoice3/BW_Comp: R79.1, U22.15 (BW_COMP)
/OSCVoice3/Expo_Freq: R78.2, R80.2, R85.2, R87.2, R89.2, R94.2, U22.6 (EXPO_FREQ)
/OSCVoice3/HF_Track: HF_Track_Trim3.3, U22.5 (HF_TRACK)
/OSCVoice3/Hard_Synch: C29.2, U15.2
/OSCVoice3/Linear_Frequency: R98.1, R99.2, U22.12 (LIN_FREQ)
/OSCVoice3/MIX_1: R92.1, R97.2, U16.1
/OSCVoice3/Op_Amp_Mix: R90.1, R91.1, R92.2, R95.1, R96.1, U16.2 (-)
/OSCVoice3/PWM_Control: C26.2, R82.1, U5.8, U22.3 (PWM_CTRL)
/OSCVoice3/PWM_Opamp_Mix: C26.1, R77.1, R81.1, R82.2, R83.1, R86.1, U5.9 (-)
/OSCVoice3/Pulse_Mix: R91.2, U15.9
/OSCVoice3/Pulse_Out: U15.8, U22.2 (PULSE_OUT)
/OSCVoice3/Saw_Mix: R95.2, U15.10
/OSCVoice3/Saw_Out: U15.11, U22.1 (SAW_OUT)
/OSCVoice3/Soft_Synch: C28.2, U8.10
/OSCVoice3/Triangle_Mix: R90.2, U15.3
/OSCVoice3/Triangle_Out: U15.4, U22.4 (TRI_OUT)
/OSCVoice4/BW_Comp: R56.1, U17.15 (BW_COMP)
/OSCVoice4/Expo_Freq: R55.2, R57.2, R62.2, R64.2, R66.2, R71.2, U17.6 (EXPO_FREQ)
/OSCVoice4/HF_Track: HF_Track_Trim4.3, U17.5 (HF_TRACK)
/OSCVoice4/Hard_Synch: C23.2, U11.2
/OSCVoice4/Linear_Frequency: R75.1, R76.2, U17.12 (LIN_FREQ)
/OSCVoice4/MIX_1: R69.1, R74.2, U18.1
/OSCVoice4/Op_Amp_Mix: R67.1, R68.1, R69.2, R72.1, R73.1, U18.2 (-)
/OSCVoice4/PWM_Control: C20.2, R59.1, U5.14, U17.3 (PWM_CTRL)
/OSCVoice4/PWM_Opamp_Mix: C20.1, R13.1, R54.1, R58.1, R59.2, R63.1, U5.13 (-)
/OSCVoice4/Pulse_Mix: R68.2, U11.9
/OSCVoice4/Pulse_Out: U11.8, U17.2 (PULSE_OUT)
/OSCVoice4/Saw_Mix: R72.2, U11.10
/OSCVoice4/Saw_Out: U11.11, U17.1 (SAW_OUT)
/OSCVoice4/Soft_Synch: C22.2, U8.2
/OSCVoice4/Triangle_Mix: R67.2, U11.3
/OSCVoice4/Triangle_Out: U11.4, U17.4 (TRI_OUT)
/PULSE_SW: J2.5, R1.2, U6.6, U7.6, U11.6, U15.6
/PWM_CV: J3.2, R15.2, R40.2, R63.2, R86.2
/PWM_CV1: J1.8, R25.2
/PWM_CV2: J2.8, R60.2
/PWM_CV3: J3.4, R83.2
/PWM_CV4: J4.6, R13.2
/PWM_POT: J3.3, R12.2, R35.2, R58.2, R81.2
/SAW_SW: J1.6, R3.2, U6.12, U7.12, U11.12, U15.12
/SOFT_SYNCH_SW: J4.2, R4.2, U8.5, U8.6, U8.12, U8.13
/SYNCH_SIGNAL1: J1.7, U6.1, U8.8
/SYNCH_SIGNAL2: J2.7, U7.1, U8.4
/SYNCH_SIGNAL3: J3.7, U8.11, U15.1
/SYNCH_SIGNAL4: J4.5, U8.1, U11.1
/TRIANGLE_SW: J4.4, R2.2, U6.5, U7.5, U11.5, U15.5
/V_PER_OCT1: J1.9, R37.1
/V_PER_OCT2: J2.9, R32.1
/V_PER_OCT3: J3.6, R78.1
/V_PER_OCT4: J4.7, R55.1
GND: Base_Freq_Trim1.1, Base_Freq_Trim2.1, Base_Freq_Trim3.1, Base_Freq_Trim4.1, C1.2, C3.2, C4.2, C7.1, C8.1, C10.2, C11.2, C12.1, C15.2, C18.2, C19.1, C21.2, C24.2, C25.1, C27.2, C30.2, C31.1, C32.2, C33.2, C34.2, C35.2, C36.2, C37.2, C38.2, C39.2, C40.2, C41.2, HF_Track_Trim1.1, HF_Track_Trim2.1, HF_Track_Trim3.1, HF_Track_Trim4.1, J1.5, J2.6, J3.5, J3.9, J4.10, J5.3, J5.4, J5.5, J5.6, J5.7, J5.8, R1.1, R2.1, R3.1, R4.1, R6.1, R9.1, R42.1, R65.1, R88.1, TP4.1, TP5.1, U1.1 (GND), U3.4 (V-), U4.1 (K), U5.3 (+), U5.5 (+), U5.10 (+), U5.11 (V-), U5.12 (+), U6.7 (VSS), U7.7 (VSS), U8.7 (VSS), U9.9 (GND), U10.3 (+), U10.5 (+), U11.7 (VSS), U12.9 (GND), U13.3 (+), U13.5 (+), U14.2 (A), U15.7 (VSS), U16.3 (+), U16.5 (+), U17.9 (GND), U18.3 (+), U18.5 (+), U22.9 (GND)
unnamed: Base_Freq_Trim1.2, R23.1
unnamed: Base_Freq_Trim2.2, R43.1
unnamed: Base_Freq_Trim3.2, R89.1
unnamed: Base_Freq_Trim4.2, R66.1
unnamed: C4.1, R10.2
unnamed: C5.1, U9.11 (SOFT_SYNC)
unnamed: C6.1, R9.2, U9.10 (HARD_SYNCH)
unnamed: C8.2, U9.8 (TCAP)
unnamed: C15.1, R33.2
unnamed: C16.1, U12.11 (SOFT_SYNC)
unnamed: C17.1, R42.2, U12.10 (HARD_SYNCH)
unnamed: C19.2, U12.8 (TCAP)
unnamed: C21.1, R56.2
unnamed: C22.1, U17.11 (SOFT_SYNC)
unnamed: C23.1, R65.2, U17.10 (HARD_SYNCH)
unnamed: C25.2, U17.8 (TCAP)
unnamed: C27.1, R79.2
unnamed: C28.1, U22.11 (SOFT_SYNC)
unnamed: C29.1, R88.2, U22.10 (HARD_SYNCH)
unnamed: C31.2, U22.8 (TCAP)
unnamed: Expo_Trim1.1, R8.2
unnamed: Expo_Trim2.1, R38.2
unnamed: Expo_Trim3.1, R84.2
unnamed: Expo_Trim4.1, R61.2
unnamed: HF_Track_Trim1.2, R16.1
unnamed: HF_Track_Trim2.2, R48.1
unnamed: HF_Track_Trim3.2, R94.1
unnamed: HF_Track_Trim4.2, R71.1
unnamed: R5.1, U3.6 (-), U3.7
unnamed: R8.1, U9.13 (EXPO_SCALE)
unnamed: R26.2, R29.1, U10.6 (-)
unnamed: R38.1, U12.13 (EXPO_SCALE)
unnamed: R47.2, R51.1, U13.6 (-)
unnamed: R61.1, U17.13 (EXPO_SCALE)
unnamed: R70.2, R74.1, U18.6 (-)
unnamed: R84.1, U22.13 (EXPO_SCALE)
unnamed: R93.2, R97.1, U16.6 (-)
unnamed: U3.1, U3.2 (-)
